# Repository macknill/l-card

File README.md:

# l-card
board repeaters for a l-card e14-140 for measuring low voltage signals

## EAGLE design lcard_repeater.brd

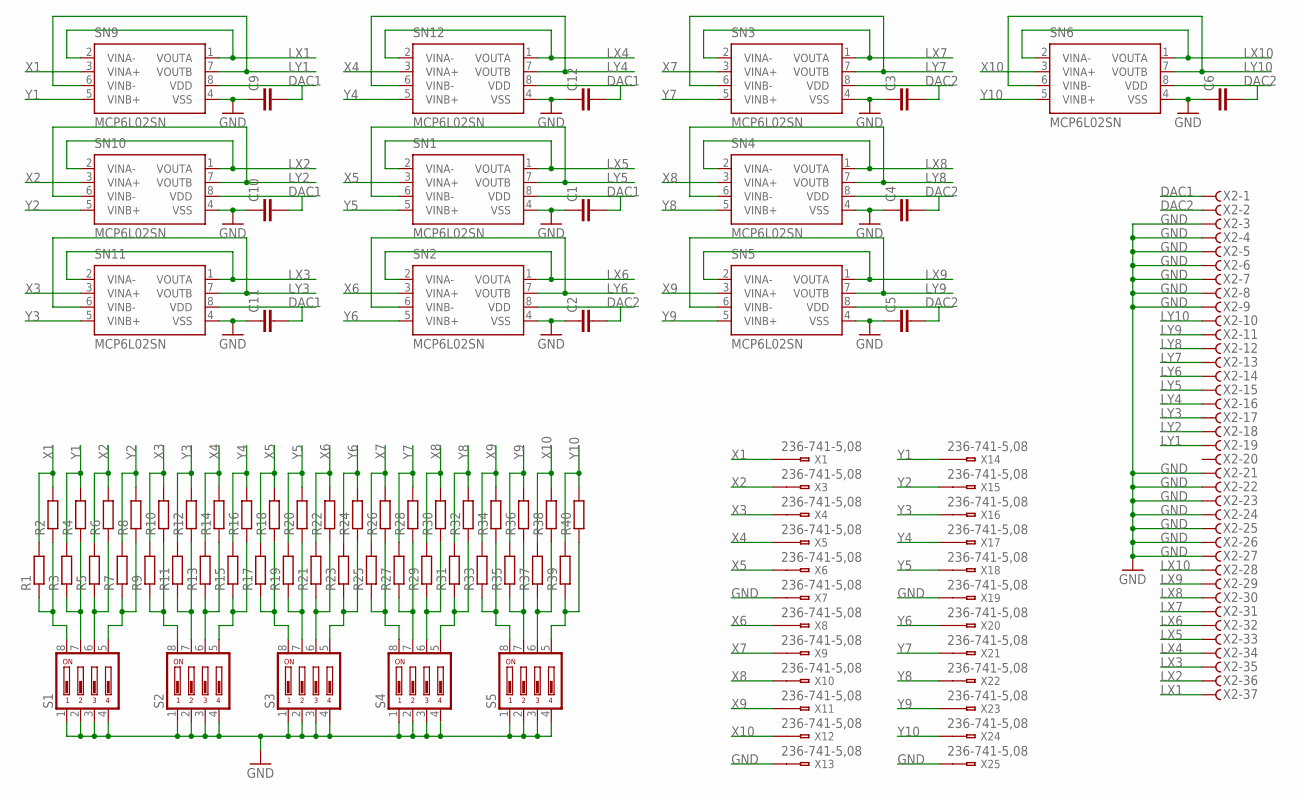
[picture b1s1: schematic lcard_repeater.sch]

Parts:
C1, C2, C3, C4, C5, C6, C9, C10, C11, C12: C-EUC1206; C1206
R1, R2, R3, R4, R5, R6, R7, R8, R9, R10, R11, R12, R13, R14, R15, R16, R17, R18, R19, R20, R21, R22, R23, R24, R25, R26, R27, R28, R29, R30, R31, R32, R33, R34, R35, R36, R37, R38, R39, R40: R-EU_R1206; R1206
S1, S2, S3, S4, S5: DS04; DS-04
SN1, SN2, SN3, SN4, SN5, SN6, SN9, SN10, SN11, SN12: MCP6L02SN; SOIC-08LG
X1, X3, X4, X5, X6, X7, X8, X9, X10, X11, X12, X13, X14, X15, X16, X17, X18, X19, X20, X21, X22, X23, X24, X25: 236-741-5,08; 236-4XX
X2: F37DS; F37D

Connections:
DAC1: C1.2, C9.2, C10.2, C11.2, C12.2, SN1.8 (VDD), SN9.8 (VDD), SN10.8 (VDD), SN11.8 (VDD), SN12.8 (VDD), X2.1
DAC2: C2.2, C3.2, C4.2, C5.2, C6.2, SN2.8 (VDD), SN3.8 (VDD), SN4.8 (VDD), SN5.8 (VDD), SN6.8 (VDD), X2.2
GND: C1.1, C2.1, C3.1, C4.1, C5.1, C6.1, C9.1, C10.1, C11.1, C12.1, S1.1, S1.2, S1.3, S1.4, S2.1, S2.2, S2.3, S2.4, S3.1, S3.2, S3.3, S3.4, S4.1, S4.2, S4.3, S4.4, S5.1, S5.2, S5.3, S5.4, SN1.4 (VSS), SN2.4 (VSS), SN3.4 (VSS), SN4.4 (VSS), SN5.4 (VSS), SN6.4 (VSS), SN9.4 (VSS), SN10.4 (VSS), SN11.4 (VSS), SN12.4 (VSS), X2.3, X2.4, X2.5, X2.6, X2.7, X2.8, X2.9, X2.21, X2.22, X2.23, X2.24, X2.25, X2.26, X2.27, X7.1@2 (B1), X13.1@2 (B1), X19.1@2 (B1), X25.1@2 (B1)
LX1: SN9.1 (VOUTA), SN9.2 (VINA-), X2.37
LX2: SN10.1 (VOUTA), SN10.2 (VINA-), X2.36
LX3: SN11.1 (VOUTA), SN11.2 (VINA-), X2.35
LX4: SN12.1 (VOUTA), SN12.2 (VINA-), X2.34
LX5: SN1.1 (VOUTA), SN1.2 (VINA-), X2.33
LX6: SN2.1 (VOUTA), SN2.2 (VINA-), X2.32
LX7: SN3.1 (VOUTA), SN3.2 (VINA-), X2.31
LX8: SN4.1 (VOUTA), SN4.2 (VINA-), X2.30
LX9: SN5.1 (VOUTA), SN5.2 (VINA-), X2.29
LX10: SN6.1 (VOUTA), SN6.2 (VINA-), X2.28
LY1: SN9.6 (VINB-), SN9.7 (VOUTB), X2.19
LY2: SN10.6 (VINB-), SN10.7 (VOUTB), X2.18
LY3: SN11.6 (VINB-), SN11.7 (VOUTB), X2.17
LY4: SN12.6 (VINB-), SN12.7 (VOUTB), X2.16
LY5: SN1.6 (VINB-), SN1.7 (VOUTB), X2.15
LY6: SN2.6 (VINB-), SN2.7 (VOUTB), X2.14
LY7: SN3.6 (VINB-), SN3.7 (VOUTB), X2.13
LY8: SN4.6 (VINB-), SN4.7 (VOUTB), X2.12
LY9: SN5.6 (VINB-), SN5.7 (VOUTB), X2.11
LY10: SN6.6 (VINB-), SN6.7 (VOUTB), X2.10
unnamed: R1.1, R2.1, S1.8
unnamed: R3.1, R4.1, S1.7
unnamed: R5.1, R6.1, S1.6
unnamed: R7.1, R8.1, S1.5
unnamed: R33.1, R34.1, S5.8
unnamed: R35.1, R36.1, S5.7
unnamed: R37.1, R38.1, S5.6
unnamed: R39.1, R40.1, S5.5
unnamed: R9.1, R10.1, S2.8
unnamed: R11.1, R12.1, S2.7
unnamed: R13.1, R14.1, S2.6
unnamed: R15.1, R16.1, S2.5
unnamed: R17.1, R18.1, S3.8
unnamed: R19.1, R20.1, S3.7
unnamed: R21.1, R22.1, S3.6
unnamed: R23.1, R24.1, S3.5
unnamed: R25.1, R26.1, S4.8
unnamed: R27.1, R28.1, S4.7
unnamed: R29.1, R30.1, S4.6
unnamed: R31.1, R32.1, S4.5
X1: R1.2, R2.2, SN9.3 (VINA+), X1.1@2 (B1)
X2: R5.2, R6.2, SN10.3 (VINA+), X3.1@2 (B1)
X3: R9.2, R10.2, SN11.3 (VINA+), X4.1@2 (B1)
X4: R13.2, R14.2, SN12.3 (VINA+), X5.1@2 (B1)
X5: R17.2, R18.2, SN1.3 (VINA+), X6.1@2 (B1)
X6: R21.2, R22.2, SN2.3 (VINA+), X8.1@2 (B1)
X7: R25.2, R26.2, SN3.3 (VINA+), X9.1@2 (B1)
X8: R29.2, R30.2, SN4.3 (VINA+), X10.1@2 (B1)
X9: R33.2, R34.2, SN5.3 (VINA+), X11.1@2 (B1)
X10: R37.2, R38.2, SN6.3 (VINA+), X12.1@2 (B1)
Y1: R3.2, R4.2, SN9.5 (VINB+), X14.1@2 (B1)
Y2: R7.2, R8.2, SN10.5 (VINB+), X15.1@2 (B1)
Y3: R11.2, R12.2, SN11.5 (VINB+), X16.1@2 (B1)
Y4: R15.2, R16.2, SN12.5 (VINB+), X17.1@2 (B1)
Y5: R19.2, R20.2, SN1.5 (VINB+), X18.1@2 (B1)
Y6: R23.2, R24.2, SN2.5 (VINB+), X20.1@2 (B1)
Y7: R27.2, R28.2, SN3.5 (VINB+), X21.1@2 (B1)
Y8: R31.2, R32.2, SN4.5 (VINB+), X22.1@2 (B1)
Y9: R35.2, R36.2, SN5.5 (VINB+), X23.1@2 (B1)
Y10: R39.2, R40.2, SN6.5 (VINB+), X24.1@2 (B1)

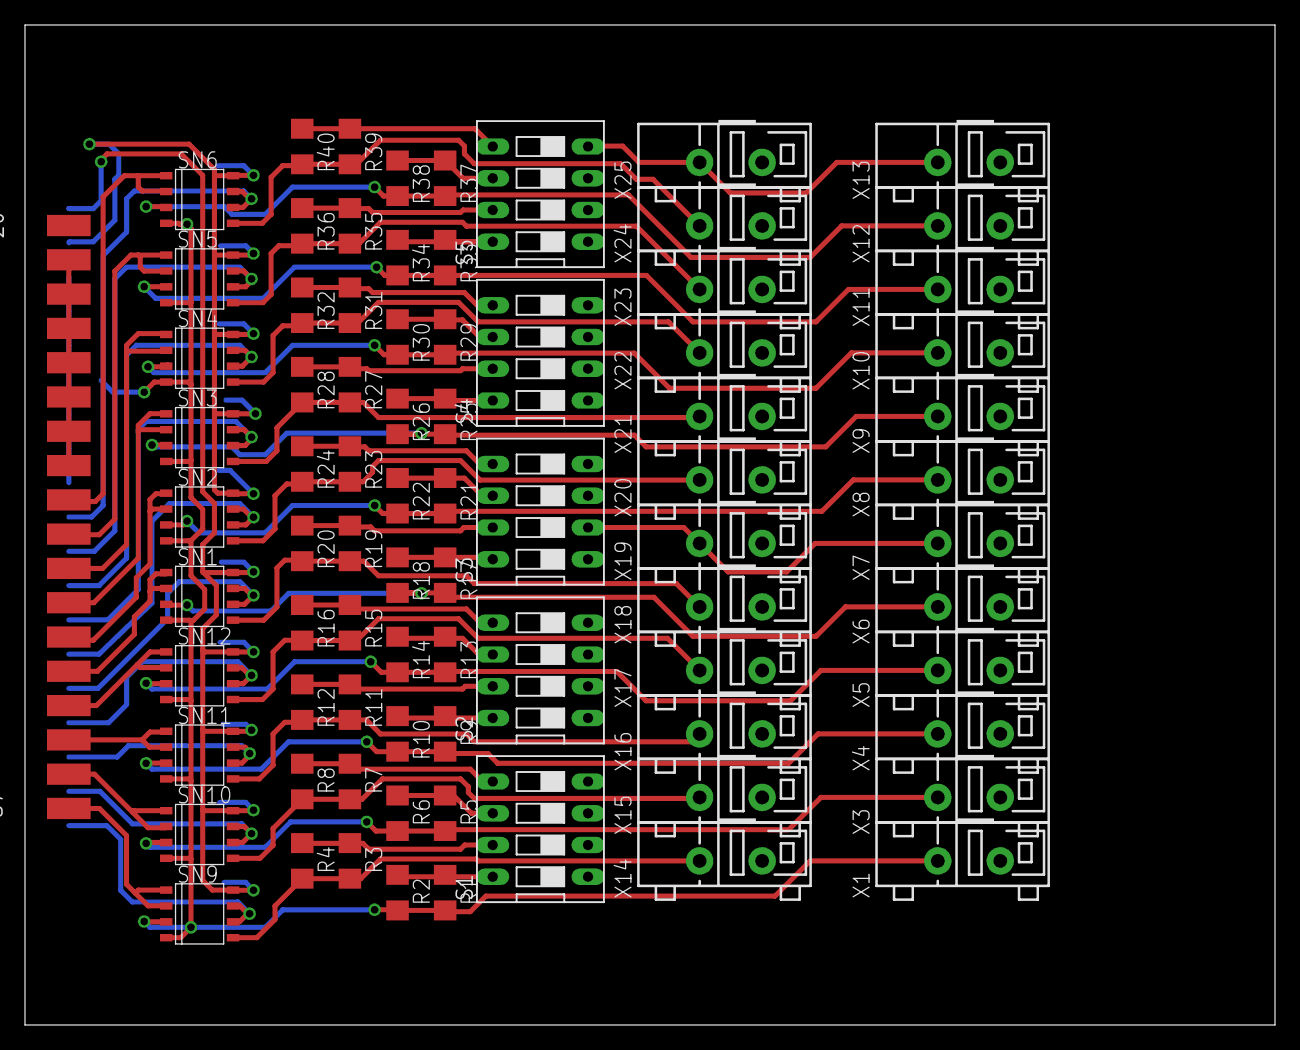
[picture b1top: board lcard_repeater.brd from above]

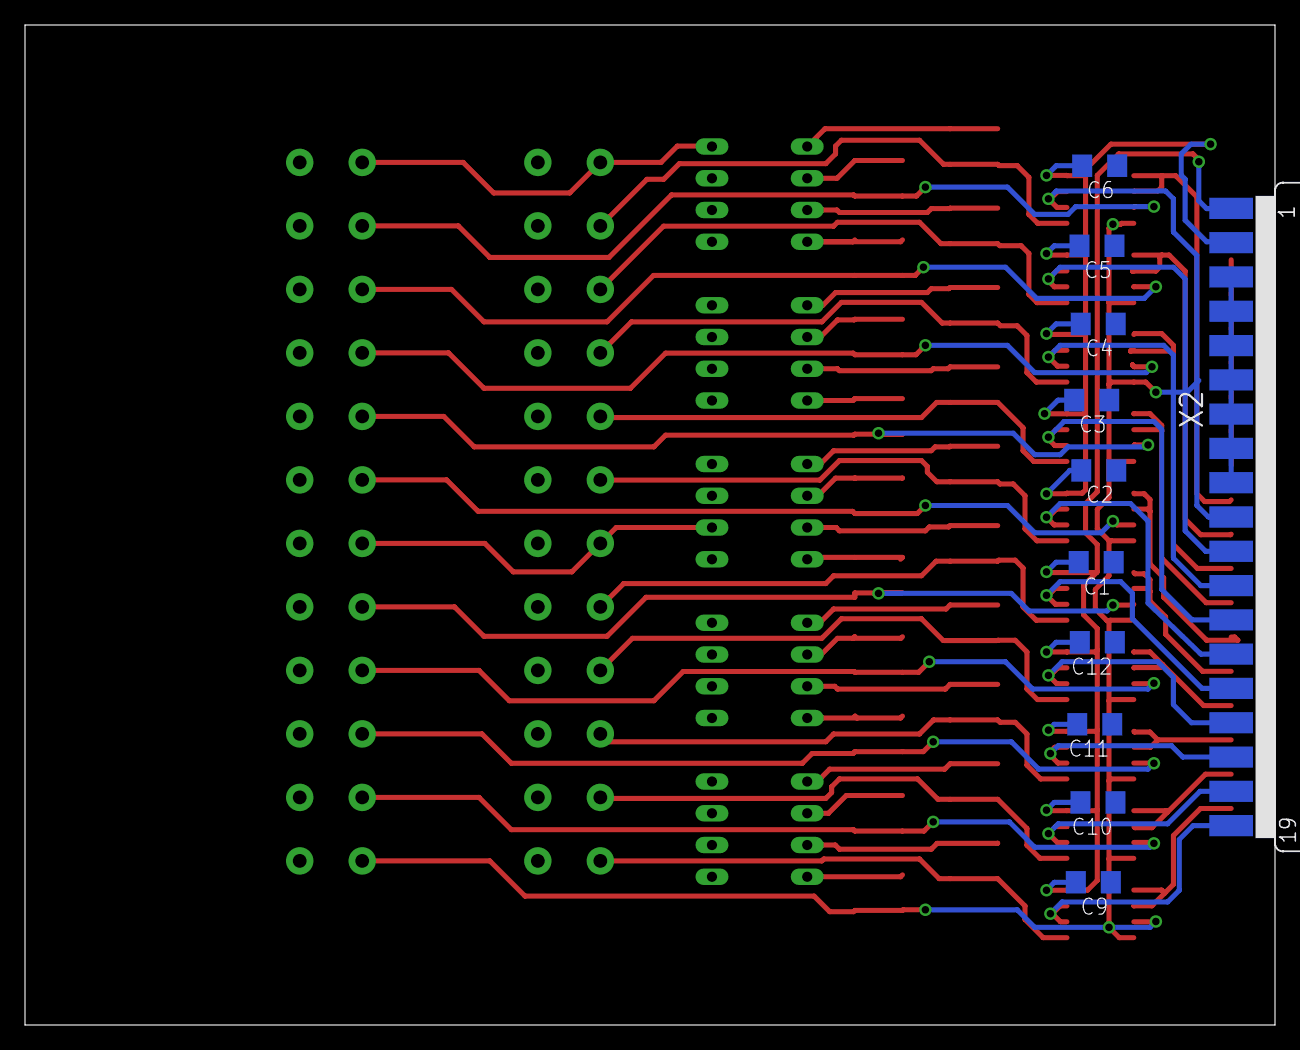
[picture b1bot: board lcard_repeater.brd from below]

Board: 2 copper layers, 100.0 x 80.0 mm, 90 parts (11 on the bottom side), 63 nets.

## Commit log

2016-03-04 add_project
    добавил проект в github
2016-03-04 Доделана схема и расставлены элементы на плате
2016-03-04 Добавил pdf для mcp6l
2016-03-04 удалил лишние файлы и добавил файл платы
2016-03-04 попытка развести плату
2016-03-10 почти развел плату, осталось немного. необходимо подсоединить конденсаторы по питанию
